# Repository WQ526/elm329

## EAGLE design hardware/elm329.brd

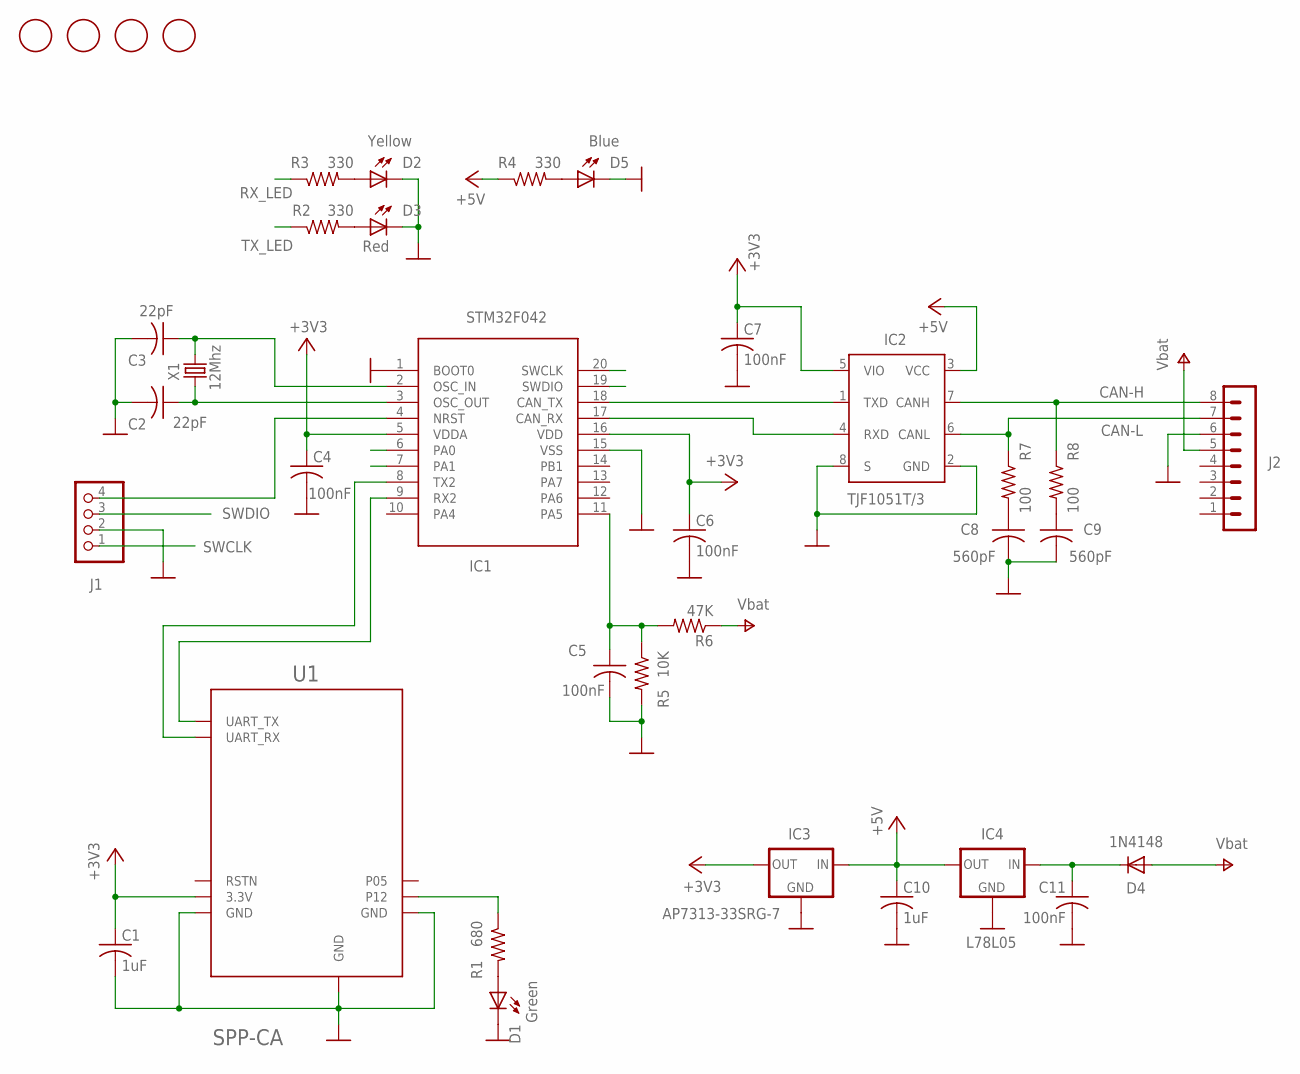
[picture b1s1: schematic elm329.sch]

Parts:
C1, C10: 1uF; C0805
C2, C3: 22pF; C0805
C4, C5, C6, C7, C11: 100nF; C0805
C8, C9: 560pF; C0805
D1: Green; CHIPLED_0805
D2: Yellow; CHIPLED_0805
D3: Red; CHIPLED_0805
D4: 1N4148; SOD123
D5: Blue; CHIPLED_0805
IC1: STM32F042; TSSOP20
IC2: TJF1051T/3; SO-8
IC3: AP7313-33SRG-7; SOT23
IC4: L78L05; SOT89R
J1: 1X04
J2: MA08-1
R1: 680; R0805
R2, R3, R4: 330; R0805
R5: 10K; R0805
R6: 47K; R0805
R7, R8: 100; R0805
U1: SPP-CA; HM-10_16
U$1, U$2, U$4, U$5: FIDUCIAL; FIDUCIAL_1MM
X1: 12Mhz; SM49

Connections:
+3V3: C1.1, C4.1, C6.1, C7.1, IC1.5 (VDDA), IC1.16 (VDD), IC2.5 (VIO), IC3.2 (OUT), U1.12 (3.3V)
+5V: C10.1, IC2.3 (VCC), IC3.3 (IN), IC4.2 (OUT), R4.1
CAN-H: IC2.7 (CANH), J2.8, R8.1
CAN-L: IC2.6 (CANL), J2.7, R7.1
CAN_RX1: IC1.17 (CAN_RX), IC2.4 (RXD)
GND: C1.2, C2.2, C3.2, C4.2, C5.2, C6.2, C7.2, C8.2, C9.2, C10.2, C11.2, D1.C, D2.C, D3.C, D5.C, IC1.1 (BOOT0), IC1.15 (VSS), IC2.2 (GND), IC2.8 (S), IC3.1 (GND), IC4.4 (GND), J1.2, J2.6, R5.2, U1.13 (GND), U1.21 (GND), U1.22 (GND)
unnamed: D1.A, R1.2
unnamed: C2.1, IC1.3 (OSC_OUT), X1.2
unnamed: IC1.4 (NRST), J1.4
unnamed: R1.1, U1.24 (P12)
unnamed: C3.1, IC1.2 (OSC_IN), X1.1
unnamed: IC1.18 (CAN_TX), IC2.1 (TXD)
unnamed: D5.A, R4.2
unnamed: IC1.9 (RX2), U1.1 (UART_TX)
unnamed: D2.A, R3.2
unnamed: D3.A, R2.2
unnamed: C11.1, D4.C, IC4.1 (IN)
unnamed: IC1.8 (TX2), U1.2 (UART_RX)
unnamed: C9.1, R8.2
unnamed: C8.1, R7.2
P0_0: C5.1, IC1.11 (PA5), R5.1, R6.2
RX_LED: IC1.7 (PA1), R3.1
SWCLK: IC1.20 (SWCLK), J1.1
SWDIO: IC1.19 (SWDIO), J1.3
TX_LED: IC1.6 (PA0), R2.1
V+: D4.A, J2.5, R6.1

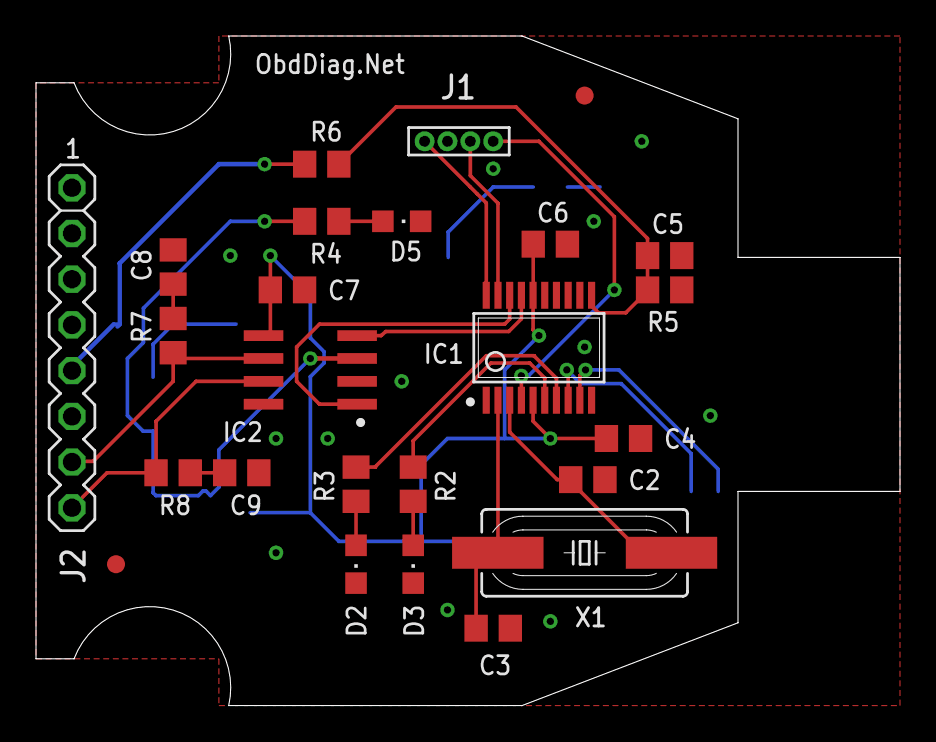
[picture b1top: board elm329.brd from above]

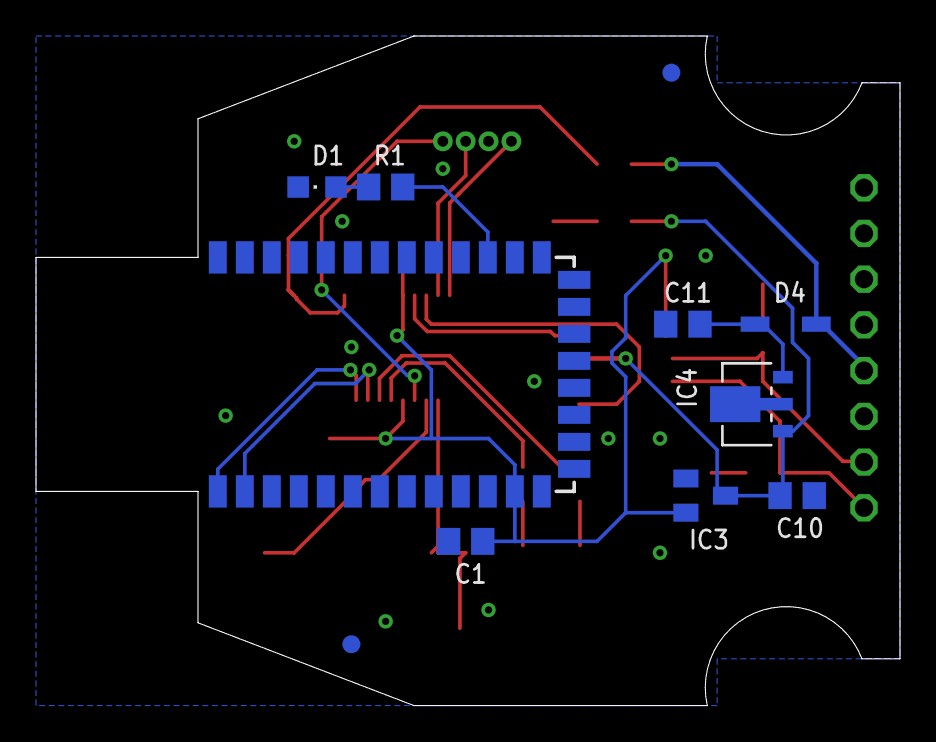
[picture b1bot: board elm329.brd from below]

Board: 2 copper layers, 48.0 x 37.2 mm, 36 parts (11 on the bottom side), 26 nets.

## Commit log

2016-10-15 Minor cleanups
2016-10-15 Minor cleanups (2)
2016-10-26 OBDII Bluetooth Mini adapter compatibility made by www.cyobd.cn
    To build for OBDII Bluetooth Mini remove -DHSE_VALUE=12000000 in C++
    compiler definitions and add -DBLUETOOTH_MINI_CFG -DPLL_SOURCE_HSI
2019-01-25 Version 1.91
2019-01-25 Updated startup settings
2019-01-25 Cleanup
2020-06-09 Added precompiled firmware and project design files
